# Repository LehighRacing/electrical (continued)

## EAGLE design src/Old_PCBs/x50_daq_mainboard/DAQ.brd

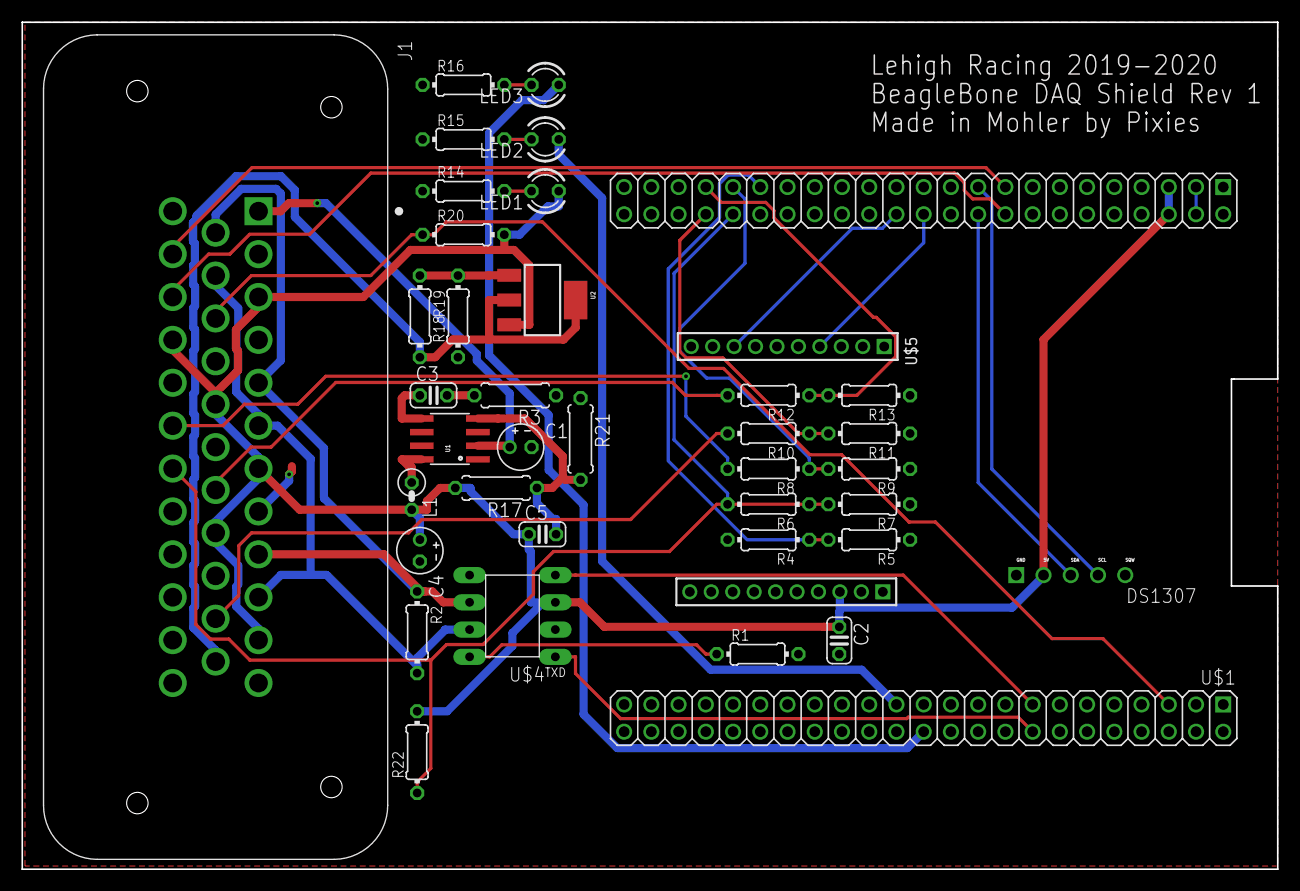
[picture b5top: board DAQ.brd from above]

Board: 2 copper layers, 117.1 x 79.0 mm, 38 parts (0 on the bottom side), 35 nets.

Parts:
C1, C4: 22u; E2-4
C2, C5: 22u; C025-024X044
C3: 3.9n; C025-024X044
J1: 1-776231-4; TE_1-776231-4
L1: 4.7u; 0207/2V
LED1, LED2, LED3: LED3MM
R1, R20: 10k; 0204/7
R2: 120; 0204/7
R3: 10k; 0207/7
R4, R6, R8, R10, R12: 100k; 0204/7
R5, R7, R9, R11, R13: 180k; 0204/7
R14, R15, R16: 220; 0204/7
R17: 24.9k; 0207/7
R18: 20k; 0204/7
R19: 12k; 0204/7
R21: 4.75k; 0207/7
R22: 4.6k; 0204/7
U1: NCP3170; SOIC8
U2: LM1117; SOT223
U$1: BEAGLEBONE_OUTLINE; BEAGLEBONE_SHIELD
U$2: DS1307; DS1307_FP
U$4: MCP2561MCP; MCP2561_PDIP
U$5: GPS

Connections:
3.3V: J1.23, R19.2, U2.2, U2.4
AIN0: R12.1, R13.2, U$1.85
AIN1: R10.1, R11.2, U$1.86
AIN2: R8.1, R9.2, U$1.83
AIN3: J1.30, R6.1, R6.2, R7.2, R22.1, U$1.84
AIN4: R4.1, R5.2, U$1.81
CAN_H: J1.6, J1.10, J1.14, R2.2, U$4.CANH
CAN_L: J1.5, J1.9, J1.13, R2.1, U$4.CANL
CAN_RX: U$1.15, U$4.RXD
CAN_TX: U$1.16, U$4.TXD
GND: C1.-, C2.2, C4.-, J1.2, J1.4, J1.8, J1.12, J1.16, J1.18, J1.21, J1.24, J1.28, R1.2, R3.1, R5.1, R7.1, R9.1, R11.1, R13.1, R14.1, R15.1, R16.1, R18.1, R21.1, U1.1, U1.3, U$1.1, U$1.2, U$1.47, U$1.48, U$1.89, U$1.90, U$1.91, U$1.92, U$2.GND, U$4.VSS, U$5.GND, U$5.GND.1
I2C1_SCL: J1.25, U$1.63
I2C1_SDA: J1.26, U$1.64
I2C2_SCL: U$1.65, U$2.SCL
I2C2_SDA: U$1.66, U$2.SDA
LAP_BTN: J1.15, R20.1, U$1.5
LOG_LED: LED2.A, U$1.25
unnamed: J1.19, R12.2
unnamed: LED1.K, R14.2
unnamed: R1.1, U$4.STBY
unnamed: LED2.K, R15.2
unnamed: LED3.K, R16.2
unnamed: J1.22, R10.2
unnamed: C3.2, R3.2
unnamed: C5.2, R17.1, R21.2, U1.4
unnamed: L1.1, U1.8
unnamed: J1.29, R8.2
unnamed: C3.1, U1.5
unnamed: R18.2, R19.1, U2.1
RAW_VIN: C1.+, J1.1, U1.2
RX-B: U$1.70, U$5.RX-B
STATUS_LED: LED3.A, U$1.24
TX-B: U$1.72, U$5.TX-B
VDD_3V3EXP: U$1.49, U$1.50
VIN: C2.1, C4.+, C5.1, J1.3, J1.7, J1.11, J1.17, J1.20, J1.27, L1.2, LED1.A, R17.2, R20.2, R22.2, U2.3, U$1.51, U$1.52, U$2.5V, U$4.VDD, U$5.VCC

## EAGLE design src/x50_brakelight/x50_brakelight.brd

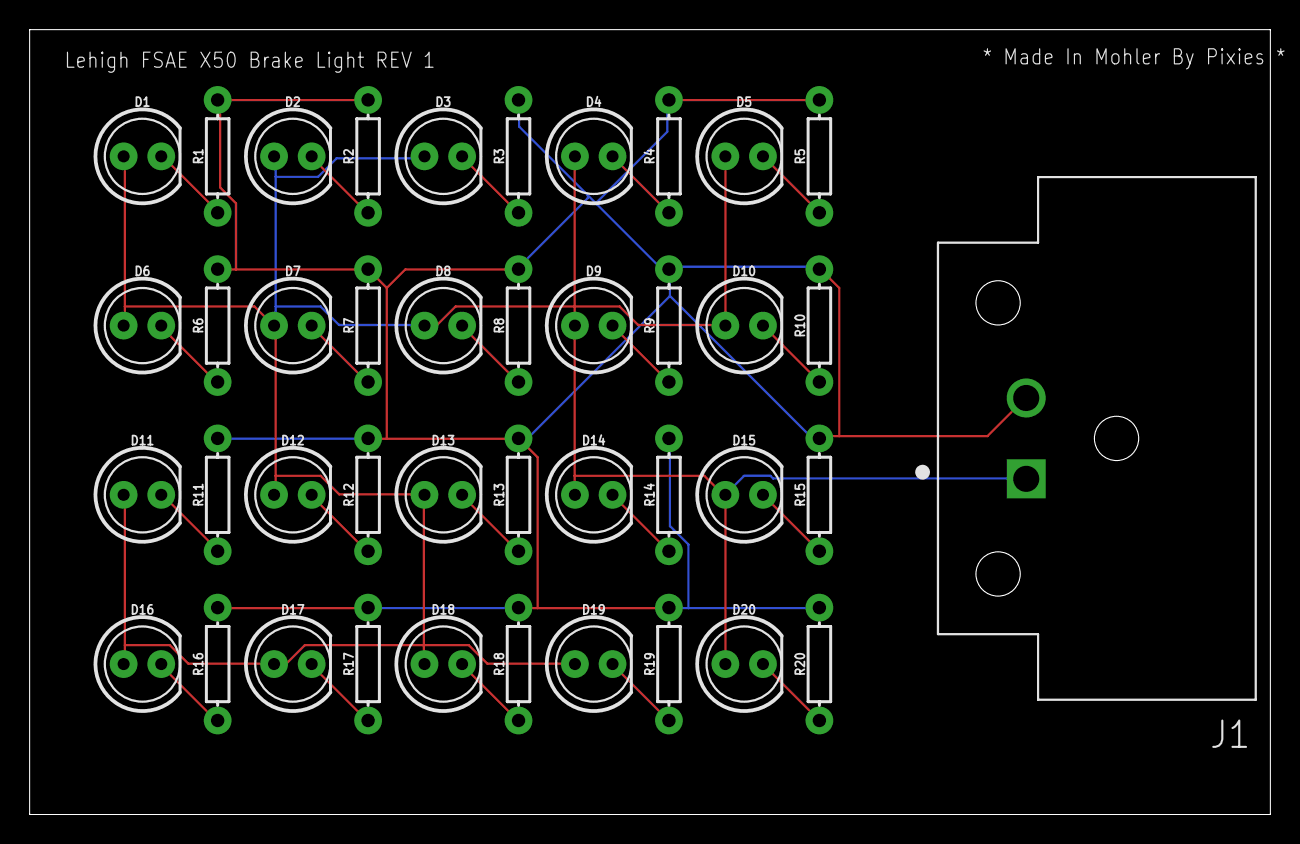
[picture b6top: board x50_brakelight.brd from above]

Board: 2 copper layers, 83.8 x 53.0 mm, 41 parts (0 on the bottom side), 22 nets.

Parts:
D1, D2, D3, D4, D5, D6, D7, D8, D9, D10, D11, D12, D13, D14, D15, D16, D17, D18, D19, D20: 560; LED_5MM
J1: DT13-2P; TE_DT13-2P
R1, R2, R3, R4, R5, R6, R7, R8, R9, R10, R11, R12, R13, R14, R15, R16, R17, R18, R19, R20: AXIAL-0.3

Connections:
GND: J1.2, R1.P$2, R2.P$2, R3.P$2, R4.P$2, R5.P$2, R6.P$2, R7.P$2, R8.P$2, R9.P$2, R10.P$2, R11.P$2, R12.P$2, R13.P$2, R14.P$2, R16.P$2, R17.P$2, R18.P$2, R19.P$2, R20.P$2
unnamed: D1.K, R1.P$1
unnamed: D2.K, R2.P$1
unnamed: D3.K, R3.P$1
unnamed: D4.K, R4.P$1
unnamed: D5.K, R5.P$1
unnamed: D6.K, R6.P$1
unnamed: D7.K, R7.P$1
unnamed: D8.K, R8.P$1
unnamed: D9.K, R9.P$1
unnamed: D10.K, R10.P$1
unnamed: D11.K, R11.P$1
unnamed: D12.K, R12.P$1
unnamed: D13.K, R13.P$1
unnamed: D14.K, R14.P$1
unnamed: D15.K, R15.P$1
unnamed: D16.K, R16.P$1
unnamed: D17.K, R17.P$1
unnamed: D18.K, R18.P$1
unnamed: D19.K, R19.P$1
unnamed: D20.K, R20.P$1
VDD_TACH: D1.A, D2.A, D3.A, D4.A, D5.A, D6.A, D7.A, D8.A, D9.A, D10.A, D11.A, D12.A, D13.A, D14.A, D15.A, D16.A, D17.A, D18.A, D19.A, D20.A, J1.1

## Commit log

2018-12-01 Add gitignore and basic tools
2018-12-01 lib/eagle: add basic formula.lbr containing MICROSQUIRT_MODULE_V2.2M
2018-12-01 lib/eagle: rename formula.lbr to microsquirt.lbr
2018-12-01 lib/eagle: Add updated description to microsquirt.lbr
2018-12-08 lib/eagle: Update microsquirt text to Names and Values layers
2019-01-08 Add X49 ECU board
2019-01-08 x49_ecu: Connect fan supply to MS FIDLE
2019-02-09 x49_ecu: revision 1a with second DTP connector
2019-02-16 x49_ecu: 1C with status LEDs
2019-03-01 x49_ecu: Rev 1D
2019-03-02 x49_ecu: Rev 1E with fixed O2 sensor gnd
2019-03-03 Add base x49_dash files
2019-03-03 x49_dash: WIP Move teensy parts closer together, clean up routing
2019-03-03 x49_dash: WIP total relayout
2019-03-03 x49_dash: Finish relayout
2019-03-03 x49_dash: Rev 1B
2019-03-03 lib/eagle: Add adafruit library for OLED 1.27inch display
2019-03-05 x49_dash: Rev 1C
2019-03-06 x49_dash: Rev 1E w/ (maybe) fixed silkscreen widths
2019-03-06 x49_dash: Rev 1F w/ (maybe) more fixed silkscreen widths
2020-10-04 Add X50 Dash Libraries
2021-04-08 LR21 Dash
2021-09-04 restructuring
2021-09-04 added CAD and restructuring
